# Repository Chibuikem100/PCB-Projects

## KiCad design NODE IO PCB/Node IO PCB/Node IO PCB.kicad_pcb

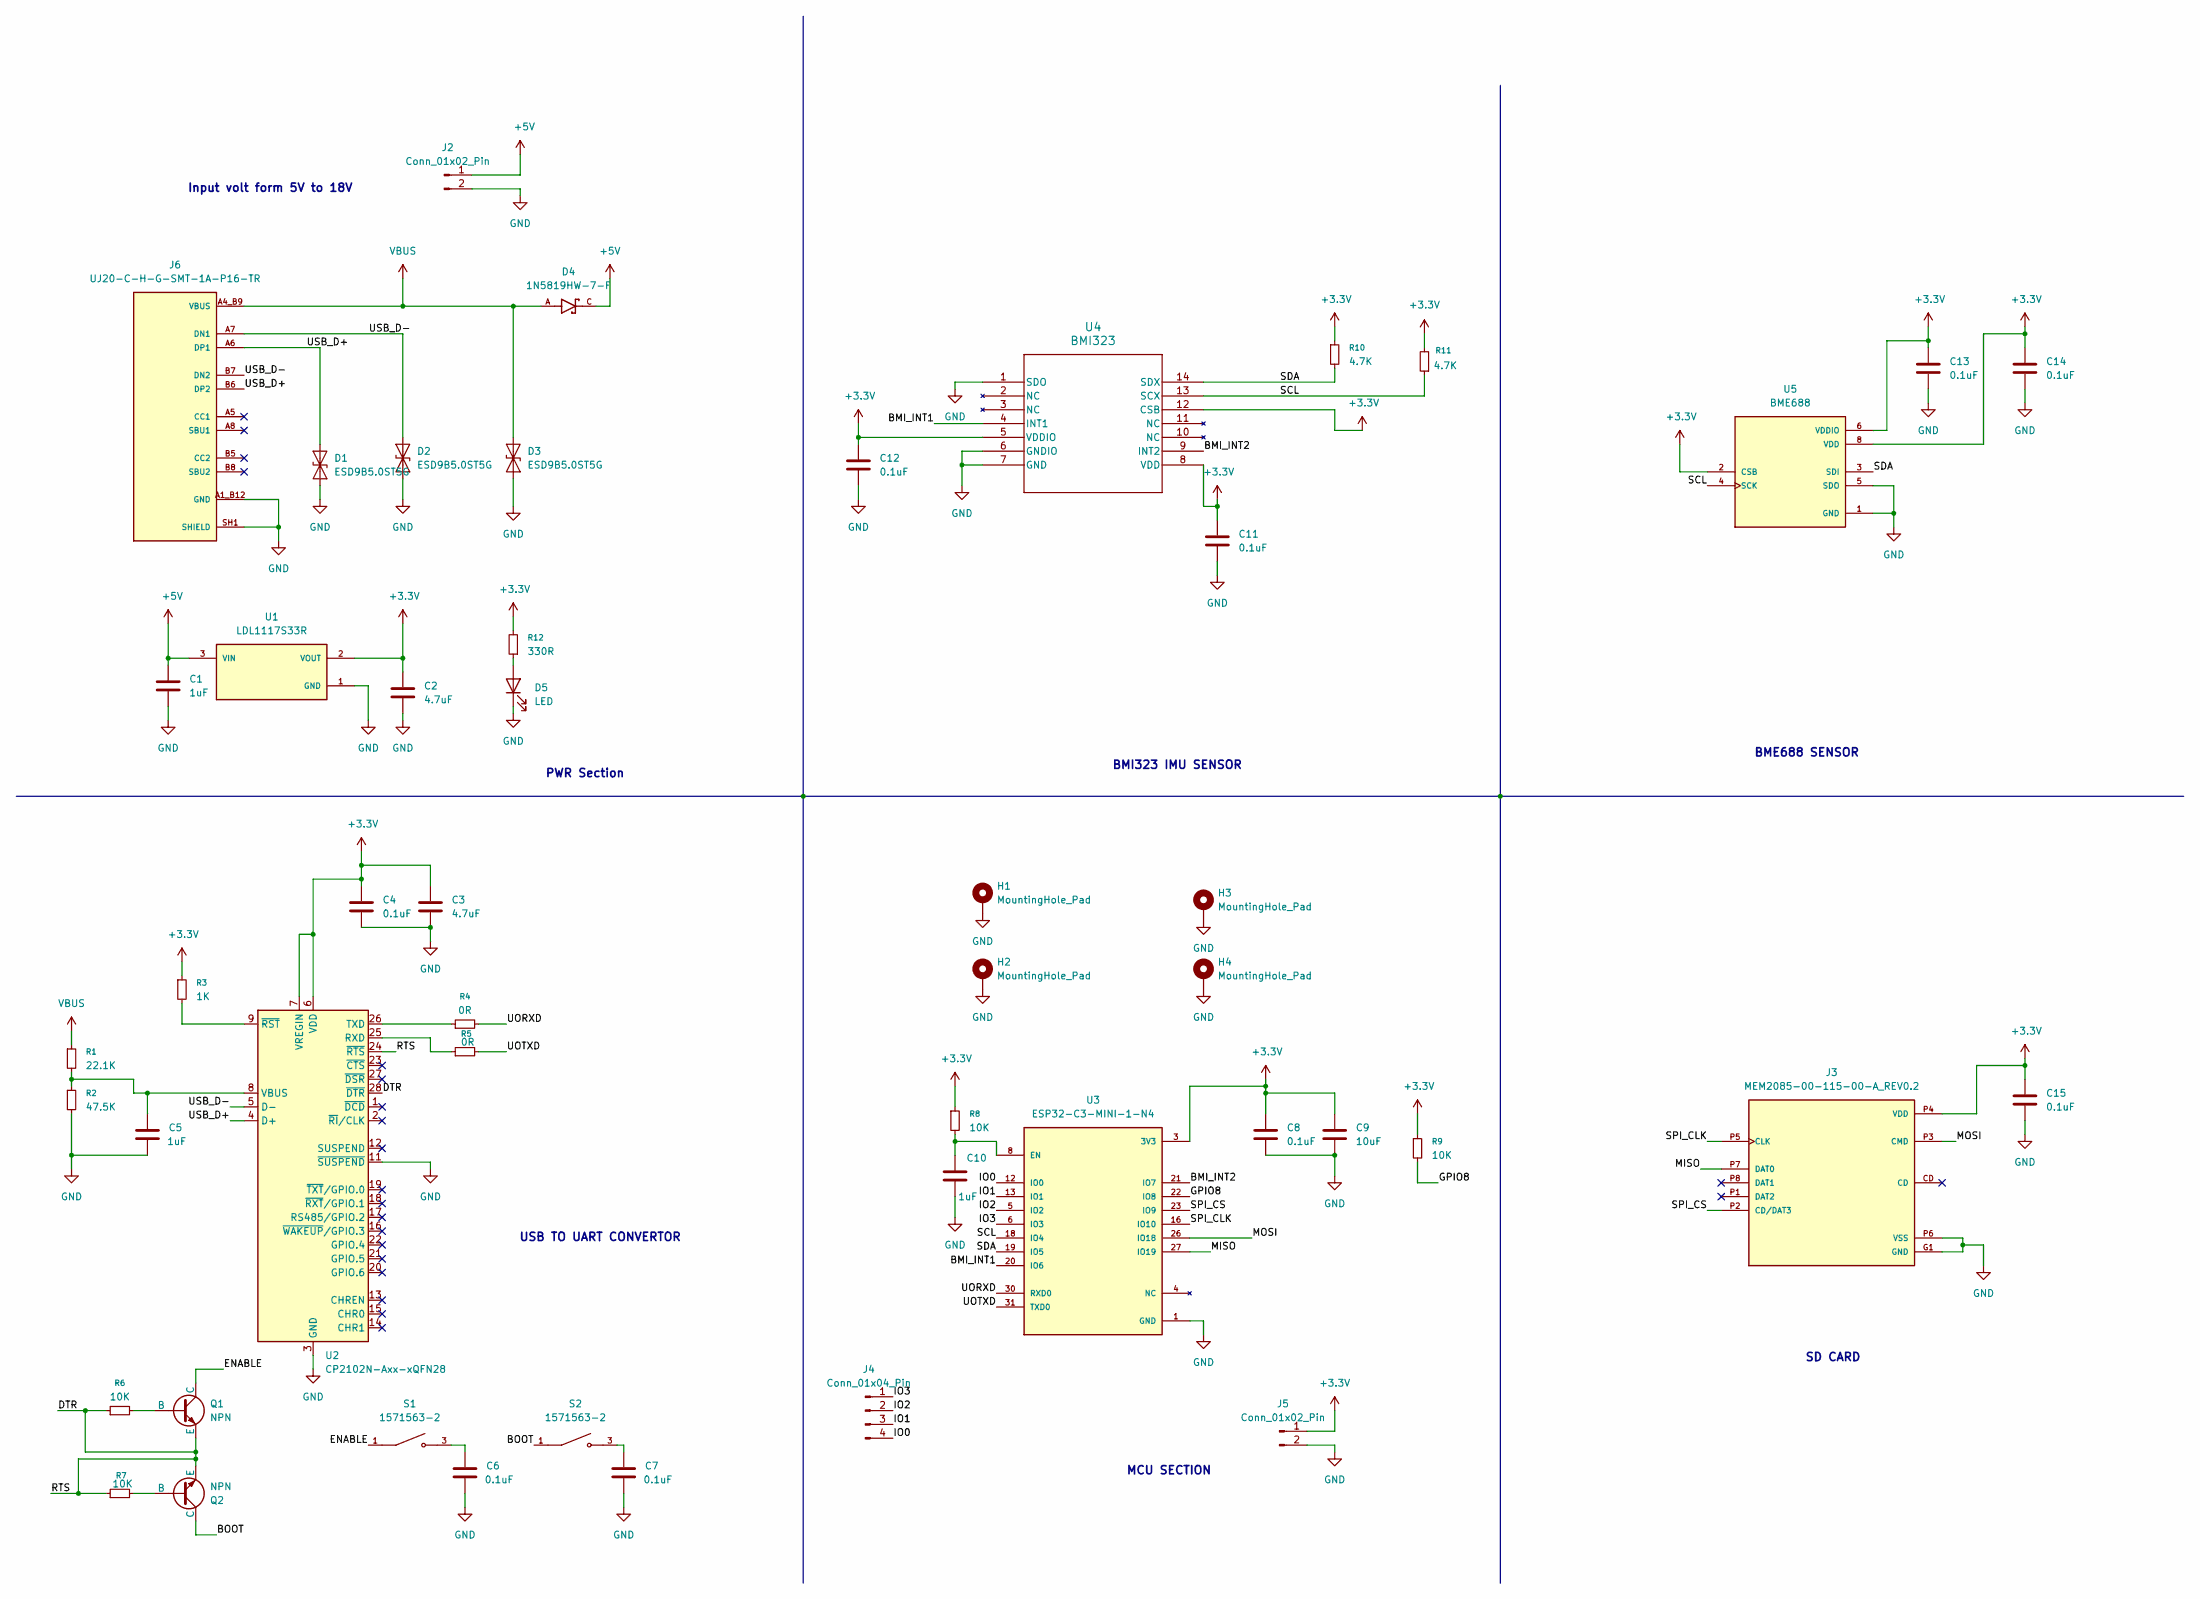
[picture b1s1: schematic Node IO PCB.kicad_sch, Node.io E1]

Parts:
C1, C5, C10: 1uF; C_0201_0603Metric
C2, C3: 4.7uF; C_0201_0603Metric
C4, C6, C7, C8, C11, C12, C13, C14, C15: 0.1uF; C_0201_0603Metric
C9: 10uF; C_0201_0603Metric
D1, D2, D3: ESD9B5.0ST5G; D_SOD-923
D4: 1N5819HW-7-F; SOD3715X145N; PARTREV 18-2
D5: LED; LED_0201_0603Metric
H1, H2, H3, H4: MountingHole_Pad; MountingHole_3mm_Pad
J2: Conn_01x02_Pin; JST_EH_S2B-EH_1x02_P2.50mm_Horizontal
J3: MEM2085-00-115-00-A_REV0.2; GCT_MEM2085-00-115-00-A_REV0.2; PARTREV 0.2
J4: Conn_01x04_Pin; PinHeader_1x04_P2.54mm_Vertical
J5: Conn_01x02_Pin; PinSocket_1x02_P2.54mm_Vertical
J6: UJ20-C-H-G-SMT-1A-P16-TR; SAMESKY_UJ20-C-H-G-SMT-1A-P16-TR; PARTREV 1.0
Q1: NPN; SOT-23-3
Q2: NPN; SOT-23
R1: 22.1K; R_0603_1608Metric
R2: 47.5K; R_0603_1608Metric
R3: 1K; R_0603_1608Metric
R4, R5: 0R; R_0603_1608Metric
R6, R7, R8, R9: 10K; R_0603_1608Metric
R10, R11: 4.7K; R_0603_1608Metric
R12: 330R; R_0603_1608Metric
S1, S2: 1571563-2; SW_1571563-2; PARTREV V
U1: LDL1117S33R; SOT230P700X180-4N; PARTREV 7
U2: CP2102N-Axx-xQFN28; QFN-28-1EP_5x5mm_P0.5mm_EP3.35x3.35mm
U3: ESP32-C3-MINI-1-N4; XCVR_ESP32-C3-MINI-1-N4; PARTREV v1.0
U4: BMI323; XDCR_BMI270
U5: BME688; IC_BME688; PARTREV 1.0

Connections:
+3.3V: C2.2, C3.1, C4.1, C8.1, C9.1, C11.1, C12.1, C13.1, C14.1, C15.1, J3.P4 (VDD), J5.1, R3.1, R8.1, R9.1, R10.1, R11.2, R12.2, U1.2 (VOUT), U1.4 (VOUT), U2.6 (VDD), U2.7 (VREGIN), U3.3 (3V3), U4.5 (VDDIO), U4.8 (VDD), U4.12 (CSB), U5.2 (CSB), U5.6 (VDDIO), U5.8 (VDD)
+5V: C1.1, D4.C, J2.1, U1.3 (VIN)
/BMI_INT1: U3.20 (IO6), U4.4 (INT1)
/BMI_INT2: U3.21 (IO7), U4.9 (INT2)
/BOOT: Q2.1 (C), S2.1, S2.2
/DTR: Q1.3 (E), Q2.3 (E), R6.1, R7.1, U2.24 (~RTS), U2.28 (~DTR)
/ENABLE: Q1.1 (C), S1.1, S1.2
/GPIO8: R9.2, U3.22 (IO8)
/IO0: J4.4, U3.12 (IO0)
/IO1: J4.3, U3.13 (IO1)
/IO2: J4.2, U3.5 (IO2)
/IO3: J4.1, U3.6 (IO3)
/MISO: J3.P7 (DAT0), U3.27 (IO19)
/MOSI: J3.P3 (CMD), U3.26 (IO18)
/SCL: R11.1, U3.18 (IO4), U4.13 (SCX), U5.4 (SCK)
/SDA: R10.2, U3.19 (IO5), U4.14 (SDX), U5.3 (SDI)
/SPI_CLK: J3.P5 (CLK), U3.16 (IO10)
/SPI_CS: J3.P2 (CD/DAT3), U3.23 (IO9)
/UORXD: R4.2, U3.30 (RXD0)
/UOTXD: R5.2, U3.31 (TXD0)
/USB_D+: D1.2 (A2), J6.A6 (DP1), J6.B6 (DP2), U2.4 (D+)
/USB_D-: D2.2 (A2), J6.A7 (DN1), J6.B7 (DN2), U2.5 (D-)
GND: C1.2, C2.1, C3.2, C4.2, C5.2, C6.2, C7.2, C8.2, C9.2, C10.2, C11.2, C12.2, C13.2, C14.2, C15.2, D1.1 (A1), D2.1 (A1), D3.1 (A1), D5.1 (K), H1.1, H2.1, H3.1, H4.1, J2.2, J3.G1 (GND), J3.G2 (GND), J3.G3 (GND), J3.G4 (GND), J3.G5 (GND), J3.G6 (GND), J3.G7 (GND), J3.G8 (GND), J3.G9 (GND), J3.G10 (GND), J3.P6 (VSS), J5.2, J6.A1_B12 (GND), J6.B1_A12 (GND), J6.SH1 (SHIELD), J6.SH2 (SHIELD), J6.SH3 (SHIELD), J6.SH4 (SHIELD), R2.2, U1.1 (GND), U2.3 (GND), U2.11 (~SUSPEND), U2.29 (GND), U3.1 (GND), U3.2 (GND), U3.11 (GND), U3.14 (GND), U3.36 (GND), U3.37 (GND), U3.38 (GND), U3.39 (GND), U3.40 (GND), U3.41 (GND), U3.42 (GND), U3.43 (GND), U3.44 (GND), U3.45 (GND), U3.46 (GND), U3.47 (GND), U3.48 (GND), U3.49_1 (GND), U3.49_2 (GND), U3.49_3 (GND), U3.49_4 (GND), U3.49_5 (GND), U3.49_6 (GND), U3.49_7 (GND), U3.49_8 (GND), U3.49_9 (GND), U3.50 (GND), U3.51 (GND), U3.52 (GND), U3.53 (GND), U4.1 (SDO), U4.6 (GNDIO), U4.7 (GND), U5.1 (GND), U5.5 (SDO), U5.7 (GND)
unnamed: C6.1, S1.3, S1.4
unnamed: C7.1, S2.3, S2.4
unnamed: D5.2 (A), R12.1
unnamed: Q1.2 (B), R6.2
unnamed: Q2.2 (B), R7.2
unnamed: R5.1, U2.25 (RXD)
unnamed: R4.1, U2.26 (TXD)
unnamed: C5.1, R1.2, R2.1, U2.8 (VBUS)
unnamed: R3.2, U2.9 (~RST)
unnamed: C10.1, R8.2, U3.8 (EN)
VBUS: D3.2 (A2), D4.A, J6.A4_B9 (VBUS), J6.B4_A9 (VBUS), R1.1

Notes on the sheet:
USB TO UART CONVERTOR
SD CARD
PWR Section
BME688 SENSOR
MCU SECTION
Input volt form 5V to 18V
BMI323 IMU SENSOR

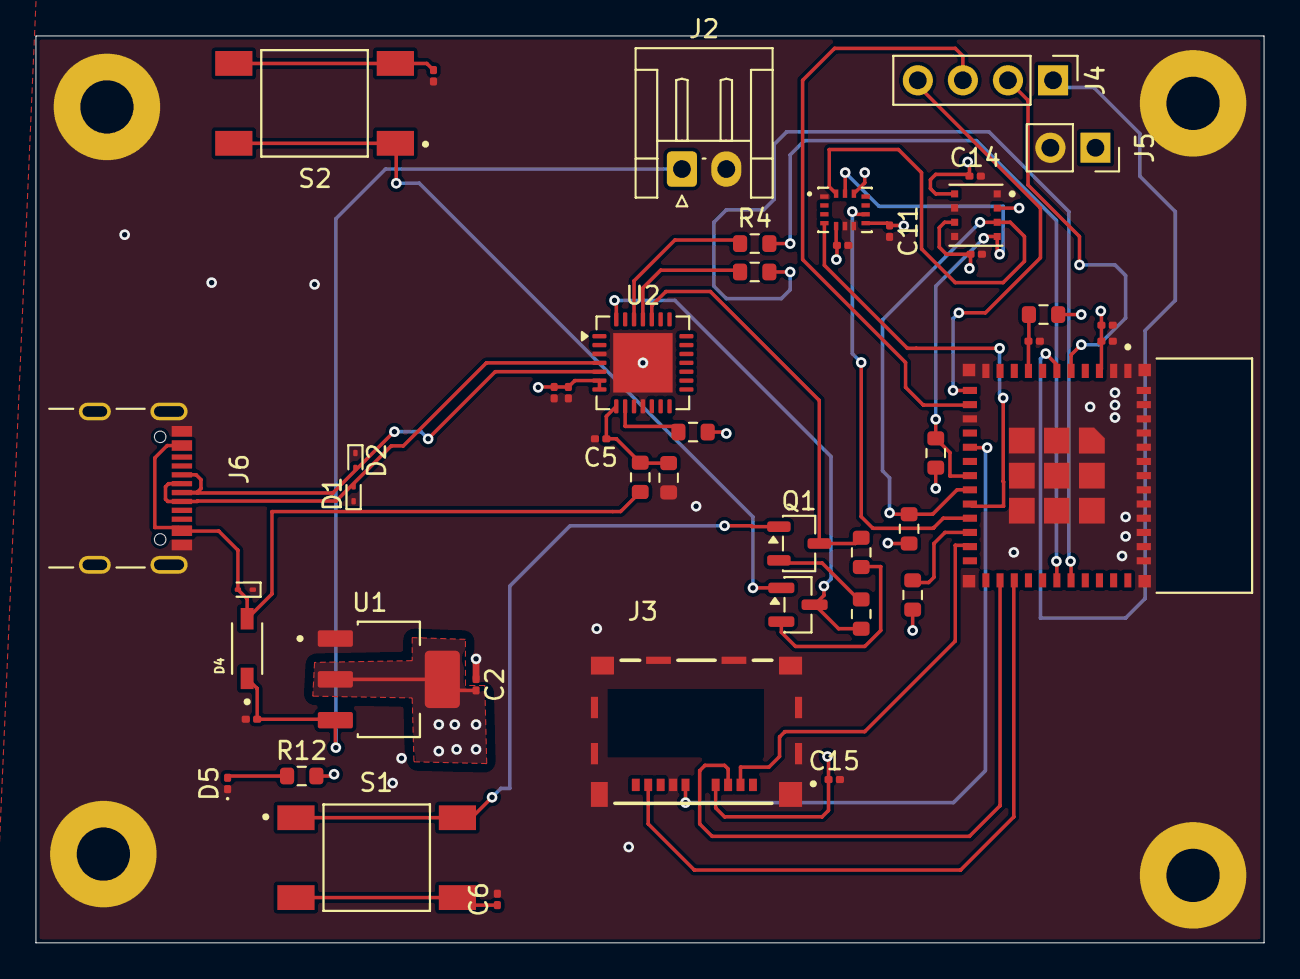
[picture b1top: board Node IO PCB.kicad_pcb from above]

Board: 4 copper layers, 69.2 x 51.1 mm, 50 parts (0 on the bottom side), 34 nets.
